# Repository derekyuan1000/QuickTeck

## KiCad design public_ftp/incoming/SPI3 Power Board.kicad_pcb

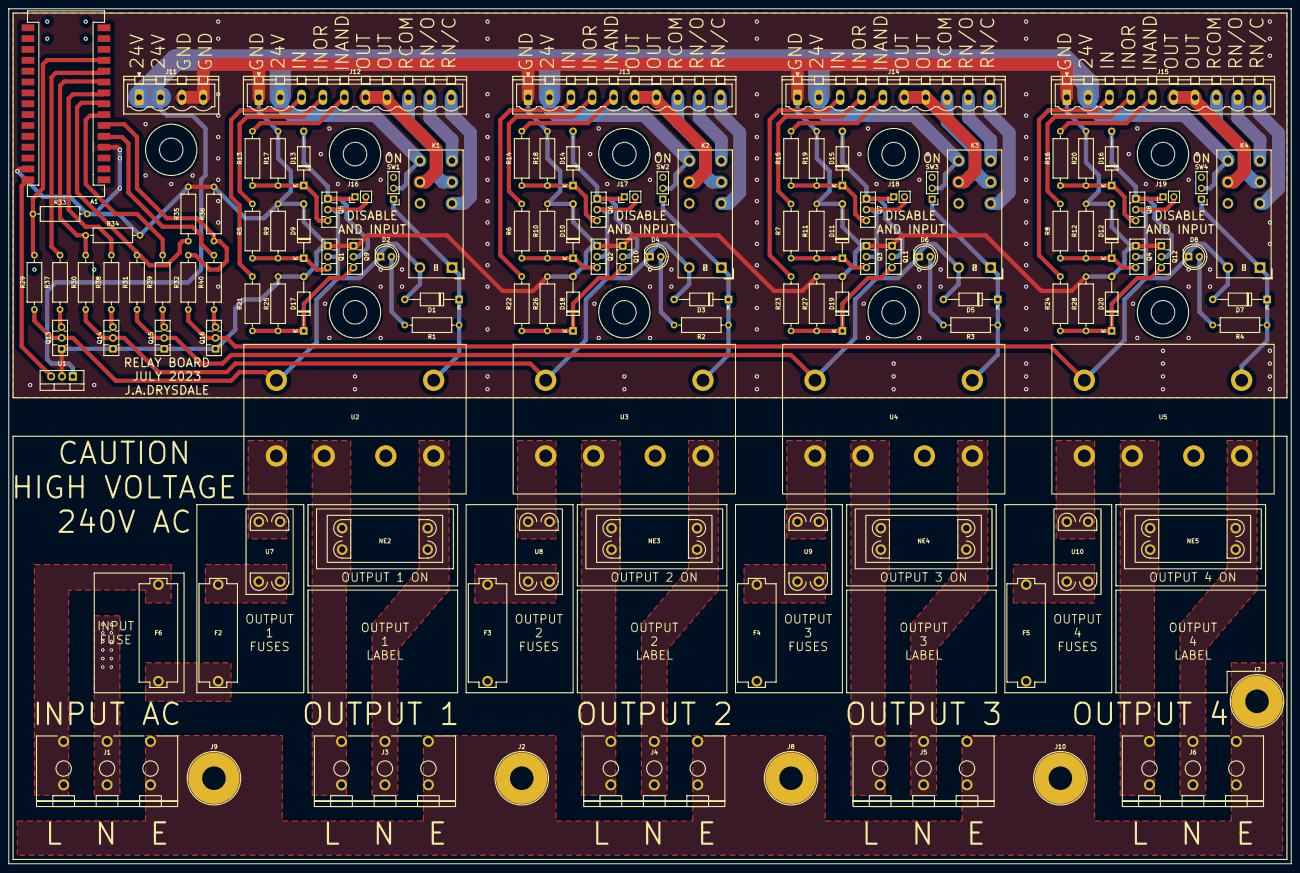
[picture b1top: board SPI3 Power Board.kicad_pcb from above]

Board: 2 copper layers, 300.0 x 200.0 mm, 122 parts (0 on the bottom side), 91 nets.

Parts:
A1: Arduino_Nano_Every; Arduino_Nano_SM
D1, D3, D5, D7: 1N4007; D_A-405_P12.70mm_Horizontal
D2, D4, D6, D8: LED; LED_D5.0mm
D9, D10, D11, D12, D13, D14, D15, D16, D17, D18, D19, D20: D_Zener; D_A-405_P12.70mm_Horizontal
F2, F3, F4, F5, F6: Fuse; FuseHolder
J1, J3, J4, J5, J6: Screw_Terminal_01x03; TerminalBlock10_16mm3P
J2, J7, J8, J9, J10: Screw_Terminal_01x01; 5mm fixing
J11: Screw_Terminal_01x04; PhoenixContact_MSTBVA_2,5_4-G_1x04_P5.00mm_Vertical
J12, J13, J14, J15: Screw_Terminal_01x10; PhoenixContact_MSTBVA_2,5_10-G_1x10_P5.00mm_Vertical
J16, J17, J18, J19: Conn_01x02_Male; PinHeader_1x02_P2.54mm_Vertical
K1, K2, K3, K4: EC2-3NU; Relay_DPDT_HF140FF
NE2, NE3, NE4, NE5: Lamp_Neon; neon lamp
Q1, Q2, Q3, Q4, Q5, Q6, Q7, Q8, Q9, Q10, Q11, Q12, Q13, Q14, Q15, Q16: BD135; TO-126-3_Vertical
R1, R2, R3, R4: 2K2; R_Axial_DIN0309_L9.0mm_D3.2mm_P12.70mm_Horizontal
R5, R6, R7, R8, R13, R14, R15, R16, R21, R22, R23, R24, R33, R34, R35, R36: 1K; R_Axial_DIN0309_L9.0mm_D3.2mm_P12.70mm_Horizontal
R9, R10, R11, R12, R17, R18, R19, R20, R25, R26, R27, R28: 10K; R_Axial_DIN0309_L9.0mm_D3.2mm_P12.70mm_Horizontal
R29, R30, R31, R32: 3K9; R_Axial_DIN0309_L9.0mm_D3.2mm_P12.70mm_Horizontal
R37, R38, R39, R40: 100R; R_Axial_DIN0309_L9.0mm_D3.2mm_P12.70mm_Horizontal
SW1, SW2, SW3, SW4: SW_SPDT; PinHeader_1x03_P2.54mm_Vertical
U1: LM7809_TO220; TO-220-3_Vertical
U2, U3, U4, U5: OMRON_G7L-2A-P-PV
U7, U8, U9, U10: ThermalTrip

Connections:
+24V: J11.1, J11.2, J12.2, J13.2, J14.2, J15.2, K1.8, K2.8, K3.8, K4.8, SW1.2 (B), SW2.2 (B), SW3.2 (B), SW4.2 (B), U1.1 (VI)
/DRIVE_1: A1.11 (D8), R37.1
/DRIVE_2: A1.9 (D6), R38.1
/DRIVE_3: A1.7 (D4), R39.1
/DRIVE_4: A1.5 (D2), R40.1
/IN_1: J12.3, R21.1
/IN_1_AND: J12.5, R13.1
/IN_1_OR: J12.4, R5.1
/IN_2: J13.3, R22.1
/IN_2_AND: J13.5, R14.1
/IN_2_OR: J13.4, R6.1
/IN_3: J14.3, R23.1
/IN_3_AND: J14.5, R15.1
/IN_3_OR: J14.4, R7.1
/IN_4: J15.3, R24.1
/IN_4_AND: J15.5, R16.1
/IN_4_OR: J15.4, R8.1
/OUT_1: J12.6, J12.7, K1.9
/OUT_2: J13.6, J13.7, K2.9
/OUT_3: J14.6, J14.7, K3.9
/OUT_4: J15.6, J15.7, K4.9
/RELAY_1_COM: J12.8, K1.4
/RELAY_1_NC: J12.10, K1.3
/RELAY_1_NO: J12.9, K1.5
/RELAY_2_COM: J13.8, K2.4
/RELAY_2_NC: J13.10, K2.3
/RELAY_2_NO: J13.9, K2.5
/RELAY_3_COM: J14.8, K3.4
/RELAY_3_NC: J14.10, K3.3
/RELAY_3_NO: J14.9, K3.5
/RELAY_4_COM: J15.8, K4.4
/RELAY_4_NC: J15.10, K4.3
/RELAY_4_NO: J15.9, K4.5
/SENSE_1: A1.12 (D9), R29.2, R33.1
/SENSE_2: A1.10 (D7), R30.2, R34.1
/SENSE_3: A1.8 (D5), R31.2, R35.1
/SENSE_4: A1.6 (D3), R32.2, R36.1
GND: A1.4 (GND), A1.29 (GND), D9.2 (A), D10.2 (A), D11.2 (A), D12.2 (A), D17.2 (A), D18.2 (A), D19.2 (A), D20.2 (A), J11.3, J11.4, J12.1, J13.1, J14.1, J15.1, Q1.1 (E), Q2.1 (E), Q3.1 (E), Q4.1 (E), Q9.1 (E), Q10.1 (E), Q11.1 (E), Q12.1 (E), Q13.1 (E), Q14.1 (E), Q15.1 (E), Q16.1 (E), R9.2, R10.2, R11.2, R12.2, R17.2, R18.2, R19.2, R20.2, R25.2, R26.2, R27.2, R28.2, R33.2, R34.2, R35.2, R36.2, U1.2 (GND)
unnamed: A1.30 (VIN), U1.3 (VO)
unnamed: D1.1 (K), K1.1, R1.1, SW1.1 (A), U2.0
unnamed: D1.2 (A), D2.1 (K), J16.2, K1.12, Q1.2 (C), Q5.2 (C), Q13.2 (C), R29.1, U2.1
unnamed: D2.2 (A), R1.2
unnamed: D3.1 (K), K2.1, R2.1, SW2.1 (A), U3.0
unnamed: D3.2 (A), D4.1 (K), J17.2, K2.12, Q2.2 (C), Q6.2 (C), Q14.2 (C), R30.1, U3.1
unnamed: D4.2 (A), R2.2
unnamed: D5.1 (K), K3.1, R3.1, SW3.1 (A), U4.0
unnamed: D5.2 (A), D6.1 (K), J18.2, K3.12, Q3.2 (C), Q7.2 (C), Q15.2 (C), R31.1, U4.1
unnamed: D6.2 (A), R3.2
unnamed: D7.1 (K), K4.1, R4.1, SW4.1 (A), U5.0
unnamed: D7.2 (A), D8.1 (K), J19.2, K4.12, Q4.2 (C), Q8.2 (C), Q16.2 (C), R32.1, U5.1
unnamed: D8.2 (A), R4.2
unnamed: D9.1 (K), Q1.3 (B), R5.2, R9.1
unnamed: D10.1 (K), Q2.3 (B), R6.2, R10.1
unnamed: D11.1 (K), Q3.3 (B), R7.2, R11.1
unnamed: D12.1 (K), Q4.3 (B), R8.2, R12.1
unnamed: D13.1 (K), Q5.3 (B), R13.2, R17.1
unnamed: D13.2 (A), J16.1, Q5.1 (E), Q9.2 (C)
unnamed: D14.1 (K), Q6.3 (B), R14.2, R18.1
unnamed: D14.2 (A), J17.1, Q6.1 (E), Q10.2 (C)
unnamed: D15.1 (K), Q7.3 (B), R15.2, R19.1
unnamed: D15.2 (A), J18.1, Q7.1 (E), Q11.2 (C)
unnamed: D16.1 (K), Q8.3 (B), R16.2, R20.1
unnamed: D16.2 (A), J19.1, Q8.1 (E), Q12.2 (C)
unnamed: D17.1 (K), Q9.3 (B), R21.2, R25.1
unnamed: D18.1 (K), Q10.3 (B), R22.2, R26.1
unnamed: D19.1 (K), Q11.3 (B), R23.2, R27.1
unnamed: D20.1 (K), Q12.3 (B), R24.2, R28.1
unnamed: F2.1, U7.1
unnamed: F2.2, F3.2, F4.2, F5.2, F6.2
unnamed: F3.1, U8.1
unnamed: F4.1, U9.1
unnamed: F5.1, U10.1
unnamed: F6.1, J1.1
unnamed: J1.2, U2.4, U3.4, U4.4, U5.4
unnamed: J1.3, J2.1, J3.3, J4.3, J5.3, J6.3, J7.1, J8.1, J9.1, J10.1
unnamed: J3.1, NE2.2, U2.6
unnamed: J3.2, NE2.1, U2.2
unnamed: J4.1, NE3.2, U3.6
unnamed: J4.2, NE3.1, U3.2
unnamed: J5.1, NE4.2, U4.6
unnamed: J5.2, NE4.1, U4.2
unnamed: J6.1, NE5.2, U5.6
unnamed: J6.2, NE5.1, U5.2
unnamed: Q13.3 (B), R37.2
unnamed: Q14.3 (B), R38.2
unnamed: Q15.3 (B), R39.2
unnamed: Q16.3 (B), R40.2
unnamed: U2.8, U7.2
unnamed: U3.8, U8.2
unnamed: U4.8, U9.2
unnamed: U5.8, U10.2

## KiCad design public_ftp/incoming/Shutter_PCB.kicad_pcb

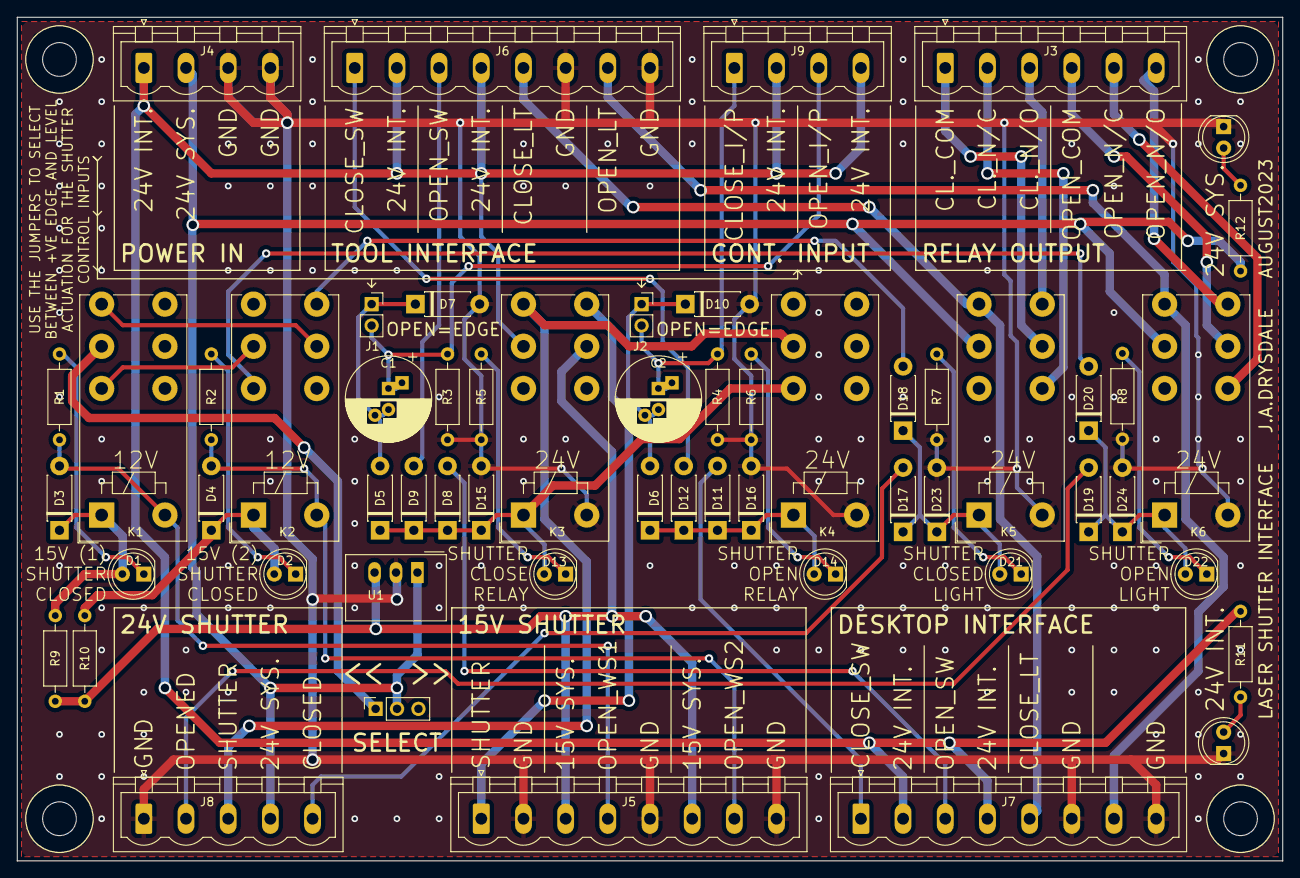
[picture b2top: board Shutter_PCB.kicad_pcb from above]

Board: 2 copper layers, 150.0 x 100.0 mm, 57 parts (0 on the bottom side), 45 nets.

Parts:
C1, C2: C_Polarized; CP_Radial_D10.0mm_P2.50mm_P5.00mm
D1, D2, D13, D14, D21, D22, D25, D26: LED; LED_D5.0mm
D3, D4, D5, D6, D7, D8, D9, D10, D11, D12, D15, D16, D17, D18, D19, D20, D23, D24: D; D_DO-41_SOD81_P7.62mm_Horizontal
J1, J2: Conn_01x02_Male; PinSocket_1x02_P2.54mm_Vertical
J3: Screw_Terminal_01x06; PhoenixContact_MSTBVA_2,5_6-G_1x06_P5.00mm_Vertical
J4, J9: Screw_Terminal_01x04; PhoenixContact_MSTBVA_2,5_4-G_1x04_P5.00mm_Vertical
J5, J6, J7: Screw_Terminal_01x08; PhoenixContact_MSTBVA_2,5_8-G_1x08_P5.00mm_Vertical
J8: Screw_Terminal_01x05; PhoenixContact_MSTBVA_2,5_5-G_1x05_P5.00mm_Vertical
K1, K2, K3, K4, K5, K6: FINDER-41.52; Relay_DPDT_Finder_40.52
R1, R2: 2K; R_Axial_DIN0207_L6.3mm_D2.5mm_P10.16mm_Horizontal
R3, R4: 1K; R_Axial_DIN0207_L6.3mm_D2.5mm_P10.16mm_Horizontal
R5, R6, R7, R8, R11, R12: 4K3; R_Axial_DIN0207_L6.3mm_D2.5mm_P10.16mm_Horizontal
R9, R10: 82R; R_Axial_DIN0207_L6.3mm_D2.5mm_P10.16mm_Horizontal
SW1: SW_SPDT; PinSocket_1x03_P2.54mm_Vertical
U1: TSR_1-24150; Converter_DCDC_TRACO_TSR-1_THT

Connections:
15V_OpensWithShutter1: D3.2 (A), J5.4, K1.A2, R1.2
15V_OpensWithShutter2: D4.2 (A), J5.7, K2.A2, R2.2
15V_SensorSupply: J5.3, J5.6, K3.21, R9.1, R10.1, U1.3 (Vout)
15V_Shutter: J5.1, K3.24
24V_Interlock: J4.1, J6.2, J6.4, J7.2, J7.4, J9.2, J9.4, K3.11, R11.1
24V_Shutter: J8.3, K3.14, K4.11
24V_ShutterClosed: D17.2 (A), J8.5
24V_ShutterOpened: D19.2 (A), J8.2
24V_System: J4.2, J8.4, K5.11, K6.11, R12.1, SW1.2 (B), U1.1 (Vin)
DesktopCloseSW: D11.2 (A), J7.1
DesktopOpenSW: D8.2 (A), J7.3
GND: D7.2 (A), D10.2 (A), D15.2 (A), D16.2 (A), D23.2 (A), D24.2 (A), D25.1 (K), D26.1 (K), J4.3, J4.4, J5.2, J5.5, J5.8, J6.6, J6.8, J7.6, J7.8, J8.1, K3.A2, K4.A2, K5.A2, K6.A2, R3.2, R4.2, R5.2, R6.2, R7.2, R8.2, U1.2 (GND)
unnamed: C1.2, D5.2 (A), D7.1 (K), J1.1
unnamed: C2.2, D6.2 (A), D10.1 (K), J2.1
unnamed: D1.1 (K), R1.1
unnamed: D1.2 (A), D3.1 (K), K1.A1, R9.2
unnamed: D2.1 (K), R2.1
unnamed: D2.2 (A), D4.1 (K), K2.A1, R10.2
unnamed: D6.1 (K), D11.1 (K), D12.1 (K), D14.2 (A), D16.1 (K), K4.A1
unnamed: D13.1 (K), R5.1
unnamed: D5.1 (K), D8.1 (K), D9.1 (K), D13.2 (A), D15.1 (K), K3.A1, K4.12
unnamed: D14.1 (K), R6.1
unnamed: D17.1 (K), D18.1 (K), D21.2 (A), D23.1 (K), K5.A1
unnamed: D18.2 (A), K2.24
unnamed: D19.1 (K), D20.1 (K), D22.2 (A), D24.1 (K), K6.A1
unnamed: D20.2 (A), K2.12
unnamed: D21.1 (K), R7.1
unnamed: D22.1 (K), R8.1
unnamed: D26.2 (A), R12.2
unnamed: K1.11, SW1.1 (A)
unnamed: K1.12, K2.11
unnamed: K1.14, K2.21
unnamed: D25.2 (A), R11.2
RelayShutterClosedCOM: J3.1, K5.21
RelayShutterClosedN/C: J3.2, K5.22
RelayShutterClosedN/O: J3.3, K5.24
RelayShutterOpenCOM: J3.4, K6.21
RelayShutterOpenN/C: J3.5, K6.22
RelayShutterOpenN/O: J3.6, K6.24
ShutterCloseSW: D12.2 (A), J6.1
ShutterCloseSignal: C2.1, J2.2, J9.1, R4.1
ShutterClosedLight: J6.5, J7.5, K5.14
ShutterOpenLight: J6.7, J7.7, K6.14
ShutterOpenSignal: C1.1, J1.2, J9.3, R3.1
shutterOpenSW: D9.2 (A), J6.3

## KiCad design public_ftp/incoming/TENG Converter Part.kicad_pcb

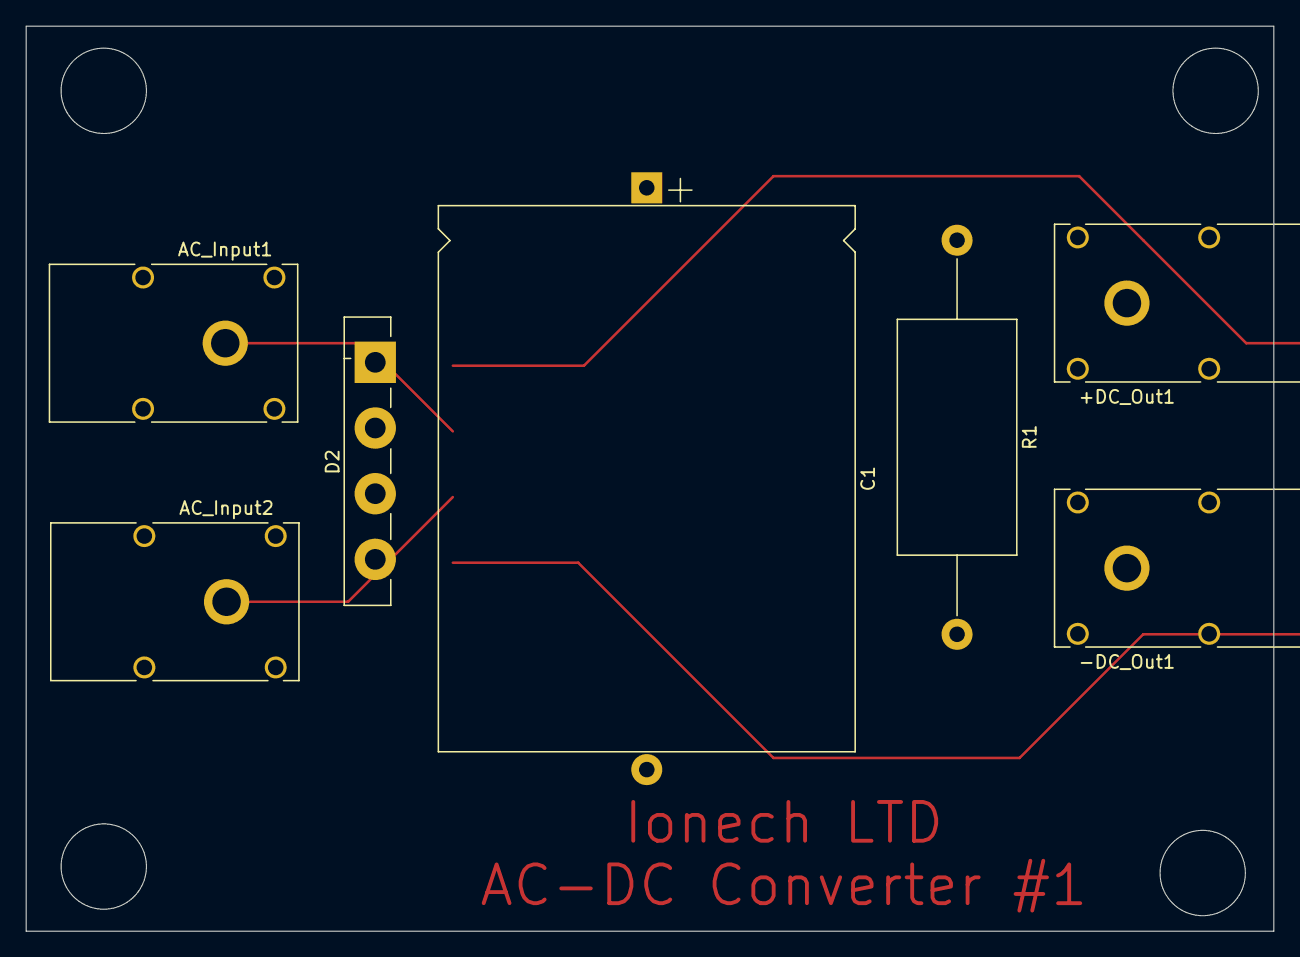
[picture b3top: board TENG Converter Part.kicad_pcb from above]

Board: 2 copper layers, 96.5 x 70.0 mm, 7 parts (0 on the bottom side), 4 nets.

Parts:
+DC_Out1: Conn_01x01_Socket; Banana_Cliff_FCR7350R_S16N-PC_Horizontal
-DC_Out1: Conn_01x01_Socket; Banana_Cliff_FCR7350B_S16N-PC_Horizontal
AC_Input1, AC_Input2: Conn_01x01_Socket; Banana_Cliff_FCR7350G_S16N-PC_Horizontal
C1: C; CP_Axial_L42.0mm_D32.0mm_P45.00mm_Horizontal
D2: Bridge Rectifier; Diode_Bridge_Vishay_GBU
R1: R; R_Axial_DIN0918_L18.0mm_D9.0mm_P30.48mm_Horizontal

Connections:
unnamed: +DC_Out1.1, C1.1, D2.1 (+), R1.1
unnamed: -DC_Out1.1, C1.2, D2.4 (-), R1.2
unnamed: AC_Input2.1, D2.3
unnamed: AC_Input1.1, D2.2

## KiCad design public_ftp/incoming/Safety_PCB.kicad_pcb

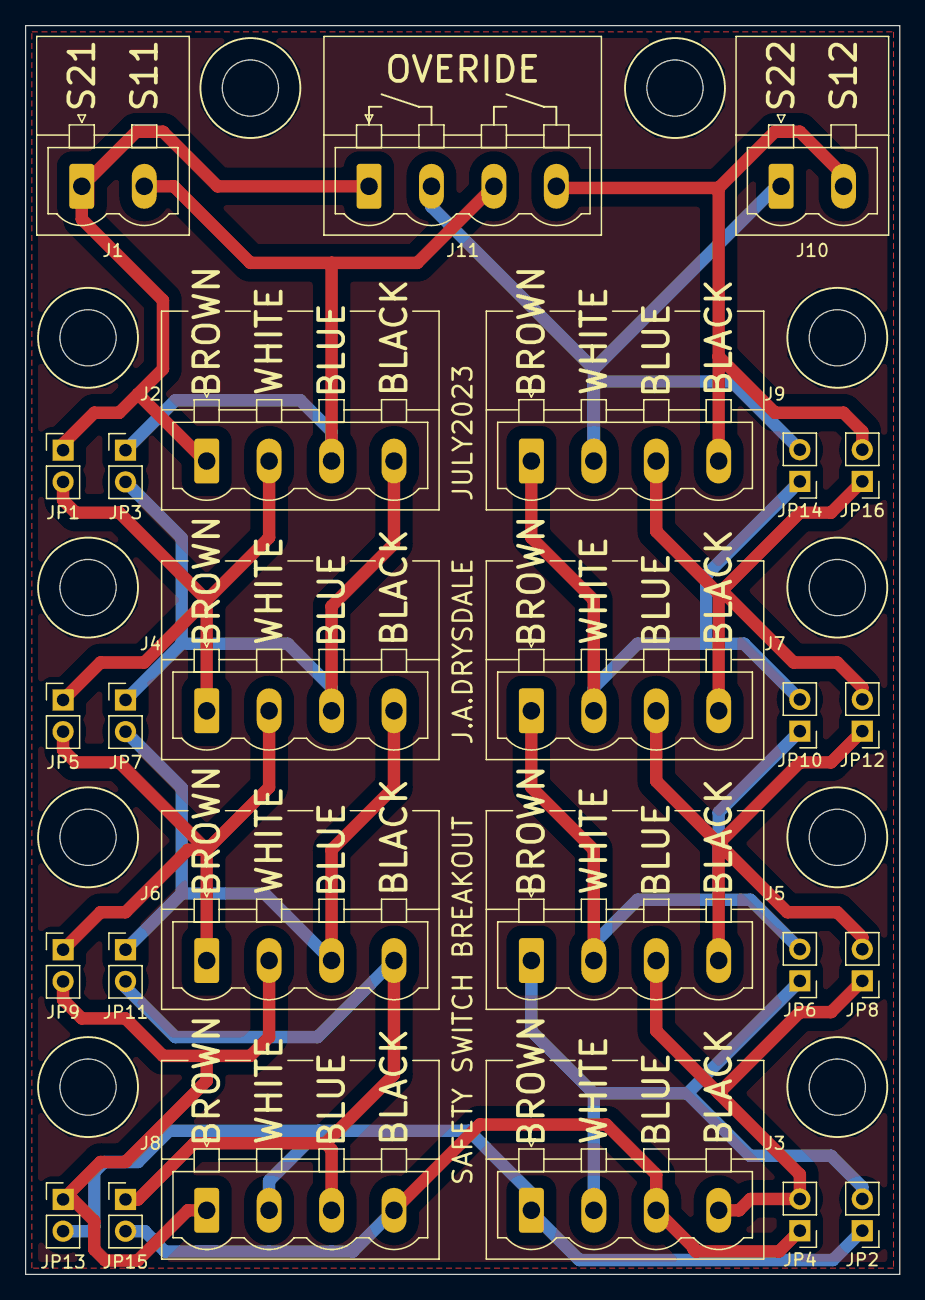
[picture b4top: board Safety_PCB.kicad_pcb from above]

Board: 2 copper layers, 70.0 x 100.0 mm, 27 parts (0 on the bottom side), 18 nets.

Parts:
J1, J10: Screw_Terminal_01x02; PhoenixContact_MSTBVA_2,5_2-G_1x02_P5.00mm_Vertical
J2, J3, J4, J5, J6, J7, J8, J9, J11: Screw_Terminal_01x04; PhoenixContact_MSTBVA_2,5_4-G_1x04_P5.00mm_Vertical
JP1, JP2, JP3, JP4, JP5, JP6, JP7, JP8, JP9, JP10, JP11, JP12, JP13, JP14, JP15, JP16: Jumper_2_Open; PinHeader_1x02_P2.54mm_Vertical

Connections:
unnamed: J1.1, J2.1, J11.1, JP1.1 (A)
unnamed: J1.2, J2.3, J11.3, JP3.1 (A)
unnamed: J2.2, J4.1, JP1.2 (B), JP5.1 (A)
unnamed: J2.4, J4.3, JP3.2 (B), JP7.1 (A)
unnamed: J3.1, J8.2, JP2.1 (A), JP13.2 (B)
unnamed: J3.2, J5.1, JP2.2 (B), JP6.1 (A)
unnamed: J3.3, J8.4, JP4.1 (A), JP15.2 (B)
unnamed: J3.4, J5.3, JP4.2 (B), JP8.1 (A)
unnamed: J4.2, J6.1, JP5.2 (B), JP9.1 (A)
unnamed: J4.4, J6.3, JP7.2 (B), JP11.1 (A)
unnamed: J5.2, J7.1, JP6.2 (B), JP10.1 (A)
unnamed: J5.4, J7.3, JP8.2 (B), JP12.1 (A)
unnamed: J6.2, J8.1, JP9.2 (B), JP13.1 (A)
unnamed: J6.4, J8.3, JP11.2 (B), JP15.1 (A)
unnamed: J7.2, J9.1, JP10.2 (B), JP14.1 (A)
unnamed: J7.4, J9.3, JP12.2 (B), JP16.1 (A)
unnamed: J9.2, J10.1, J11.2, JP14.2 (B)
unnamed: J9.4, J10.2, J11.4, JP16.2 (B)

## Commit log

2025-06-30 Track large file with Git LFS
